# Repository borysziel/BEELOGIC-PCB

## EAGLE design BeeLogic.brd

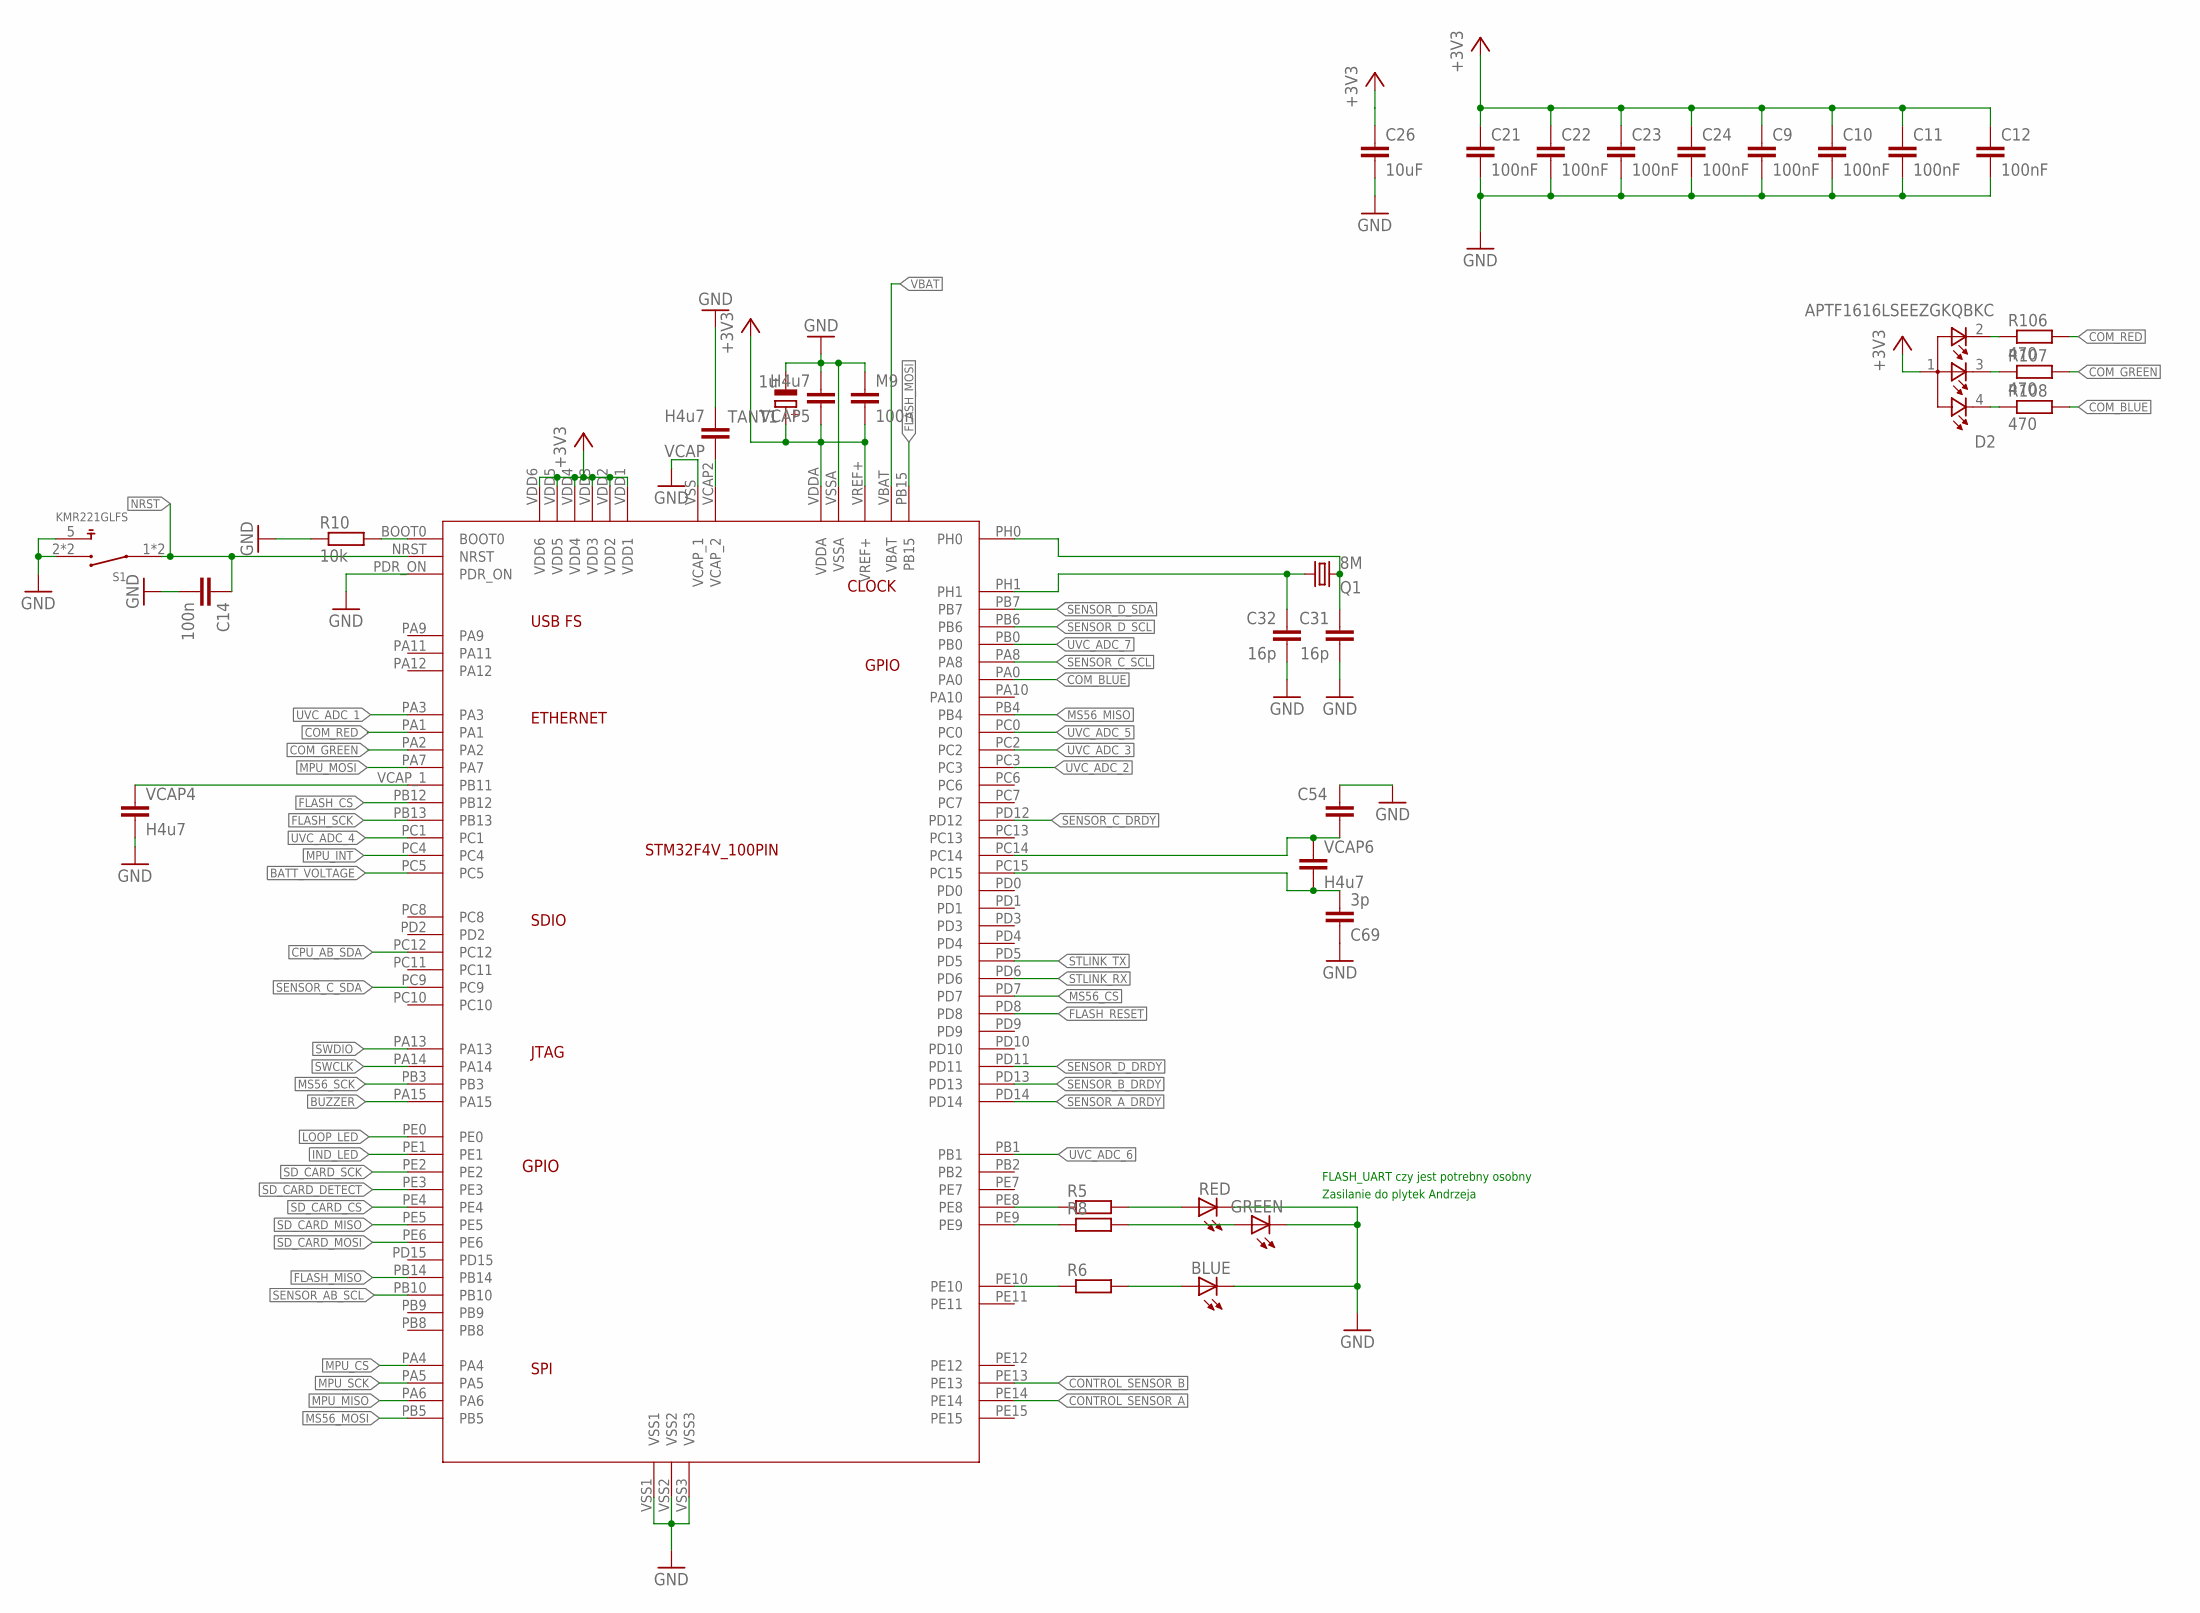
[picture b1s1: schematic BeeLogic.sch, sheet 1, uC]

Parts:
BLUE: LEDCHIPLED_0603; CHIPLED_0603
C9, C10, C11, C12, C21, C22, C23, C24: 100nF; C0603K
C14: 100n; C0603K
C26: 10uF; C0805K
C31, C32: 16p; C0603K
C54, C69: 3p; C0603K
D2: APTF1616LSEEZGKQBKC; LEDSC160X160X070-4N
GREEN: LEDCHIPLED_0603; CHIPLED_0603
M9: 100n; C0603K
Q1: 8M; CTS406
R5, R6, R8: R-EU_R0603; R0603
R10: 10k; R0603
R106, R107, R108: 470; R0603
RED: LEDCHIPLED_0603; CHIPLED_0603
S1: KMR221GLFS; SW_KMR221GLFS
STM32F446VET1: STM32F4V_100PIN_GPSBOARD; LQFP100
TANT1: 1u; SMC_A
VCAP, VCAP4, VCAP5, VCAP6: H4u7; C0805K

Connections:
+3V3: C9.1, C10.1, C11.1, C12.1, C21.1, C22.1, C23.1, C24.1, C26.1, D2.1, M9.2, STM32F446VET1.VDD1, STM32F446VET1.VDD2, STM32F446VET1.VDD3, STM32F446VET1.VDD4, STM32F446VET1.VDD5, STM32F446VET1.VDD6, STM32F446VET1.VDDA, STM32F446VET1.VREF+, TANT1.+, VCAP5.1; also elsewhere on the board
BATT_VOLTAGE: STM32F446VET1.PC5; also elsewhere on the board
BUZZER: STM32F446VET1.PA15; also elsewhere on the board
COM_BLUE: R108.2, STM32F446VET1.PA0
COM_GREEN: R107.2, STM32F446VET1.PA2
COM_RED: R106.2, STM32F446VET1.PA1
CONTROL_SENSOR_A: STM32F446VET1.PE14; also elsewhere on the board
CONTROL_SENSOR_B: STM32F446VET1.PE13; also elsewhere on the board
CPU_AB_SDA: STM32F446VET1.PC12; also elsewhere on the board
FLASH_CS: STM32F446VET1.PB12; also elsewhere on the board
FLASH_MISO: STM32F446VET1.PB14; also elsewhere on the board
FLASH_MOSI: STM32F446VET1.PB15; also elsewhere on the board
FLASH_RESET: STM32F446VET1.PD8; also elsewhere on the board
FLASH_SCK: STM32F446VET1.PB13; also elsewhere on the board
GND: BLUE.C, C9.2, C10.2, C11.2, C12.2, C14.2, C21.2, C22.2, C23.2, C24.2, C26.2, C31.2, C32.2, C54.2, C69.1, GREEN.C, M9.1, R10.1, RED.C, S1.2 (3), S1.3, S1.5, STM32F446VET1.PDR_ON, STM32F446VET1.VSS (VCAP_1), STM32F446VET1.VSS1, STM32F446VET1.VSS2, STM32F446VET1.VSS3, STM32F446VET1.VSSA, TANT1.-, VCAP.2, VCAP4.2, VCAP5.2; also elsewhere on the board
IND_LED: STM32F446VET1.PE1; also elsewhere on the board
LOOP_LED: STM32F446VET1.PE0; also elsewhere on the board
MPU_CS: STM32F446VET1.PA4; also elsewhere on the board
MPU_INT: STM32F446VET1.PC4; also elsewhere on the board
MPU_MISO: STM32F446VET1.PA6; also elsewhere on the board
MPU_MOSI: STM32F446VET1.PA7; also elsewhere on the board
MPU_SCK: STM32F446VET1.PA5; also elsewhere on the board
MS56_CS: STM32F446VET1.PD7; also elsewhere on the board
MS56_MISO: STM32F446VET1.PB4; also elsewhere on the board
MS56_MOSI: STM32F446VET1.PB5; also elsewhere on the board
MS56_SCK: STM32F446VET1.PB3; also elsewhere on the board
unnamed: R5.1, STM32F446VET1.PE8
unnamed: R8.1, STM32F446VET1.PE9
unnamed: R6.1, STM32F446VET1.PE10
unnamed: R10.2, STM32F446VET1.BOOT0
unnamed: C31.1, Q1.3 (2), STM32F446VET1.PH0
unnamed: C32.1, Q1.1, STM32F446VET1.PH1
unnamed: R5.2, RED.A
unnamed: GREEN.A, R8.2
unnamed: BLUE.A, R6.2
unnamed: STM32F446VET1.VCAP2 (VCAP_2), VCAP.1
unnamed: STM32F446VET1.VCAP_1 (PB11), VCAP4.1
unnamed: D2.2, R106.1
unnamed: D2.3, R107.1
unnamed: D2.4, R108.1
unnamed: C54.1, STM32F446VET1.PC14, VCAP6.1
unnamed: C69.2, STM32F446VET1.PC15, VCAP6.2
NRST: C14.1, S1.1, S1.4 (1), STM32F446VET1.NRST; also elsewhere on the board
SD_CARD_CS: STM32F446VET1.PE4; also elsewhere on the board
SD_CARD_DETECT: STM32F446VET1.PE3; also elsewhere on the board
SD_CARD_MISO: STM32F446VET1.PE5; also elsewhere on the board
SD_CARD_MOSI: STM32F446VET1.PE6; also elsewhere on the board
SD_CARD_SCK: STM32F446VET1.PE2; also elsewhere on the board
SENSOR_AB_SCL: STM32F446VET1.PB10; also elsewhere on the board
SENSOR_A_DRDY: STM32F446VET1.PD14; also elsewhere on the board
SENSOR_B_DRDY: STM32F446VET1.PD13; also elsewhere on the board
SENSOR_C_DRDY: STM32F446VET1.PD12; also elsewhere on the board
SENSOR_C_SCL: STM32F446VET1.PA8; also elsewhere on the board
SENSOR_C_SDA: STM32F446VET1.PC9; also elsewhere on the board
SENSOR_D_DRDY: STM32F446VET1.PD11; also elsewhere on the board
SENSOR_D_SCL: STM32F446VET1.PB6; also elsewhere on the board
SENSOR_D_SDA: STM32F446VET1.PB7; also elsewhere on the board
STLINK_RX: STM32F446VET1.PD6; also elsewhere on the board
STLINK_TX: STM32F446VET1.PD5; also elsewhere on the board
SWCLK: STM32F446VET1.PA14; also elsewhere on the board
SWDIO: STM32F446VET1.PA13; also elsewhere on the board
UVC_ADC_1: STM32F446VET1.PA3; also elsewhere on the board
UVC_ADC_2: STM32F446VET1.PC3; also elsewhere on the board
UVC_ADC_3: STM32F446VET1.PC2; also elsewhere on the board
UVC_ADC_4: STM32F446VET1.PC1; also elsewhere on the board
UVC_ADC_5: STM32F446VET1.PC0; also elsewhere on the board
UVC_ADC_6: STM32F446VET1.PB1; also elsewhere on the board
UVC_ADC_7: STM32F446VET1.PB0; also elsewhere on the board
VBAT: STM32F446VET1.VBAT; also elsewhere on the board

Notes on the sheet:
FLASH_UART czy jest potrebny osobny
Zasilanie do plytek Andrzeja

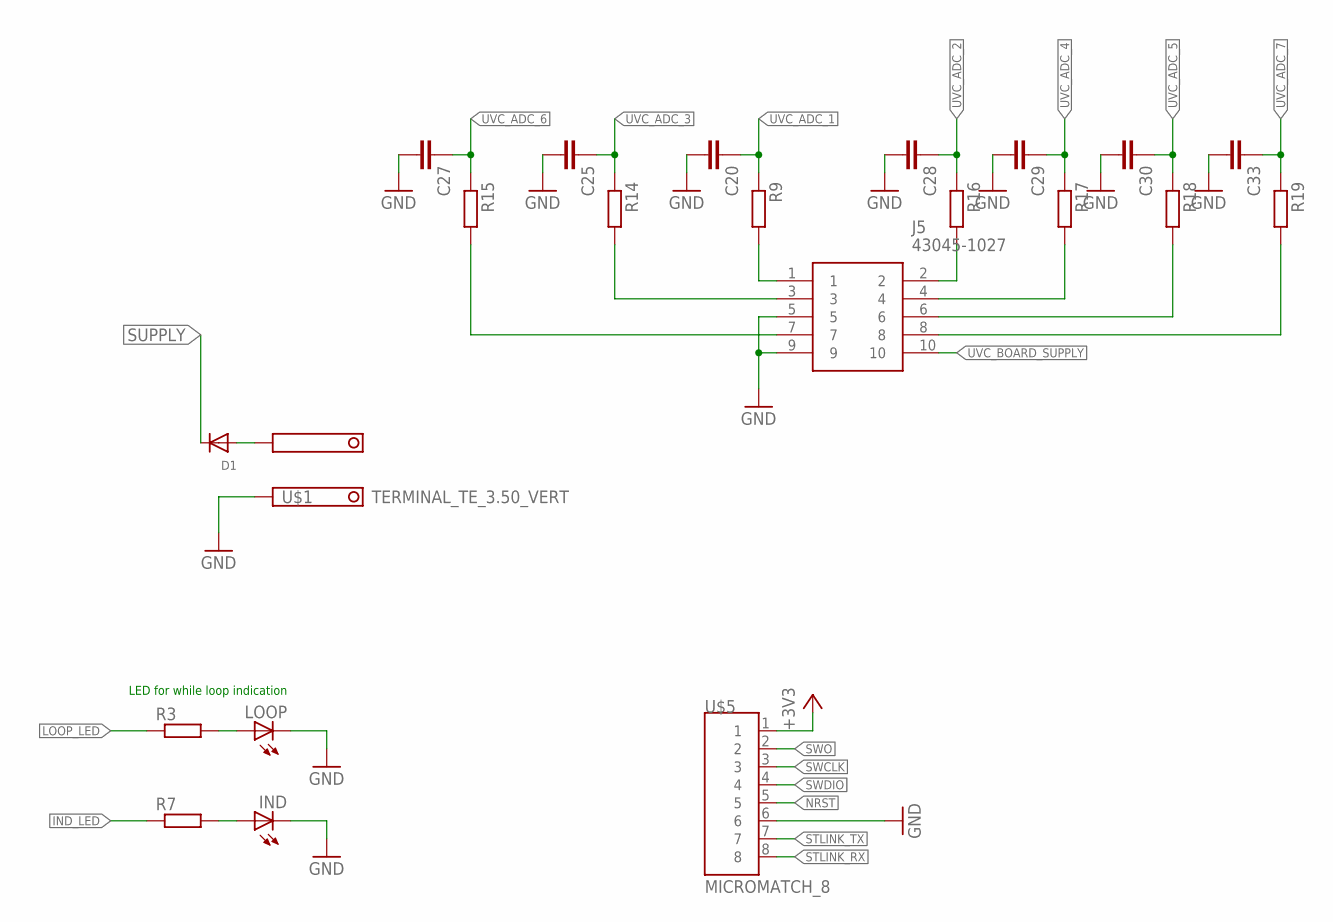
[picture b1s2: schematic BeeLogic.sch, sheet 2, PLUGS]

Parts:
C20, C25, C27, C28, C29, C30, C33: C-EUC0603; C0603
D1: DIODE_SOD-123FL; SOD-123FL
IND: LEDCHIPLED_0603; CHIPLED_0603
J5: 43045-1027; 43045-1028_1
LOOP: LEDCHIPLED_0603; CHIPLED_0603
R3, R7, R9, R14, R15, R16, R17, R18, R19: R-EU_R0603; R0603
U$1: TERMINAL_TE_3.50_VERT; TE_3.5_TERMINAL_VERT
U$5: MICROMATCH_8

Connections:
+3V3: U$5.1; also elsewhere on the board
GND: C20.2, C25.2, C27.2, C28.2, C29.2, C30.2, C33.2, IND.C, J5.5, J5.9, LOOP.C, U$1.P$2 (K1), U$5.6; also elsewhere on the board
IND_LED: R7.1; also elsewhere on the board
LOOP_LED: R3.1; also elsewhere on the board
unnamed: LOOP.A, R3.2
unnamed: D1.A, U$1.P$1 (K)
unnamed: IND.A, R7.2
unnamed: J5.1, R9.2
unnamed: J5.7, R15.2
unnamed: J5.3, R14.2
unnamed: J5.2, R16.2
unnamed: J5.4, R17.2
unnamed: J5.6, R18.2
unnamed: J5.8, R19.2
NRST: U$5.5; also elsewhere on the board
STLINK_RX: U$5.8; also elsewhere on the board
STLINK_TX: U$5.7; also elsewhere on the board
SUPPLY: D1.C; also elsewhere on the board
SWCLK: U$5.3; also elsewhere on the board
SWDIO: U$5.4; also elsewhere on the board
SWO: U$5.2
UVC_ADC_1: C20.1, R9.1; also elsewhere on the board
UVC_ADC_2: C28.1, R16.1; also elsewhere on the board
UVC_ADC_3: C25.1, R14.1; also elsewhere on the board
UVC_ADC_4: C29.1, R17.1; also elsewhere on the board
UVC_ADC_5: C30.1, R18.1; also elsewhere on the board
UVC_ADC_6: C27.1, R15.1; also elsewhere on the board
UVC_ADC_7: C33.1, R19.1; also elsewhere on the board
UVC_BOARD_SUPPLY: J5.10; also elsewhere on the board

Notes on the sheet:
LED for while loop indication

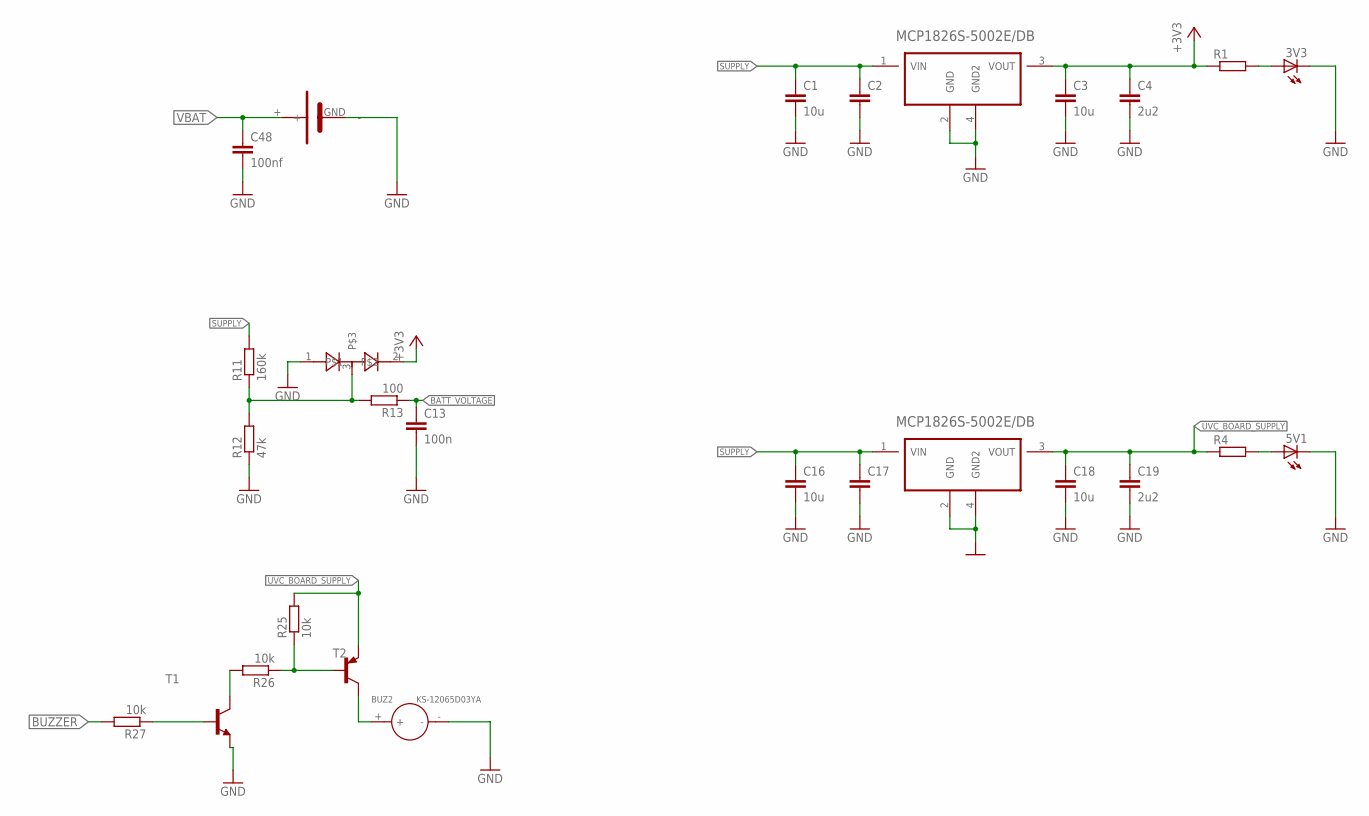
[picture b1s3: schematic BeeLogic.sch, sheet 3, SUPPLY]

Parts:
3V3, 5V1: LEDCHIPLED_0603; CHIPLED_0603
BUZ2: KS-12065D03YA; BZ2-7.6-D12.0XH6.5MM
C1, C3, C16, C18: 10u; C0805K
C2, C17: C-EUC0805K; C0805K
C4, C19: 2u2; C0805K
C13: 100n; C0603
C48: 100nf; C0805K
R1, R4: R-EU_R0603; R0603
R11: 160k; R0603
R12: 47k; R0603
R13: 100; R0603
R25, R26, R27: 10k; R0603
T1: BCW81-NPN-SOT23-BEC; SOT23-BEC
T2: BC807-16-PNP-SOT23-BEC; SOT23-BEC
U1, U3: MCP1826S-5002E/DB; SOT230P700X180-4N
U$16: BAS40W-04; SOT65P210X110-3N
U$32: CR1220_POZ

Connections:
+3V3: C3.1, C4.1, R1.1, U1.3 (VOUT), U$16.2; also elsewhere on the board
BATT_VOLTAGE: C13.1, R13.1; also elsewhere on the board
BUZZER: R27.2; also elsewhere on the board
GND: 3V3.C, 5V1.C, BUZ2.-, C1.2, C2.2, C3.2, C4.2, C13.2, C16.2, C17.2, C18.2, C19.2, C48.2, R12.1, T1.E, U1.2 (GND), U1.4 (GND2), U3.2 (GND), U3.4 (GND2), U$16.1, U$32.GND (-); also elsewhere on the board
unnamed: 3V3.A, R1.2
unnamed: 5V1.A, R4.2
unnamed: R11.1, R12.2, R13.2, U$16.3
unnamed: R25.1, R26.1, T2.B
unnamed: BUZ2.+, T2.C
unnamed: R26.2, T1.C
unnamed: R27.1, T1.B
SUPPLY: C1.1, C2.1, C16.1, C17.1, R11.2, U1.1 (VIN), U3.1 (VIN); also elsewhere on the board
UVC_BOARD_SUPPLY: C18.1, C19.1, R4.1, R25.2, T2.E, U3.3 (VOUT); also elsewhere on the board
VBAT: C48.1, U$32.+; also elsewhere on the board

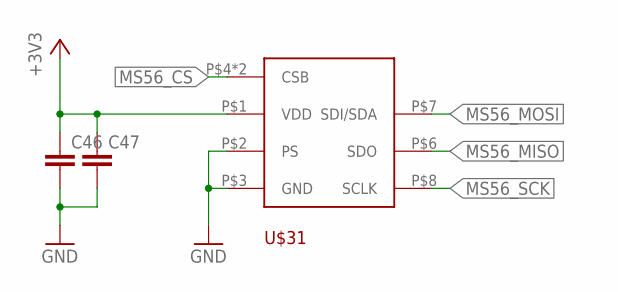
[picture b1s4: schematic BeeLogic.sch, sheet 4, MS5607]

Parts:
C46, C47: C-EUC0603; C0603
U$31: MS56XX

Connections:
+3V3: C46.1, C47.1, U$31.P$1 (VDD); also elsewhere on the board
GND: C46.2, C47.2, U$31.P$2 (PS), U$31.P$3 (GND); also elsewhere on the board
MS56_CS: U$31.P$4 (CSB), U$31.P$5 (CSB); also elsewhere on the board
MS56_MISO: U$31.P$6 (SDO); also elsewhere on the board
MS56_MOSI: U$31.P$7 (SDI/SDA); also elsewhere on the board
MS56_SCK: U$31.P$8 (SCLK); also elsewhere on the board

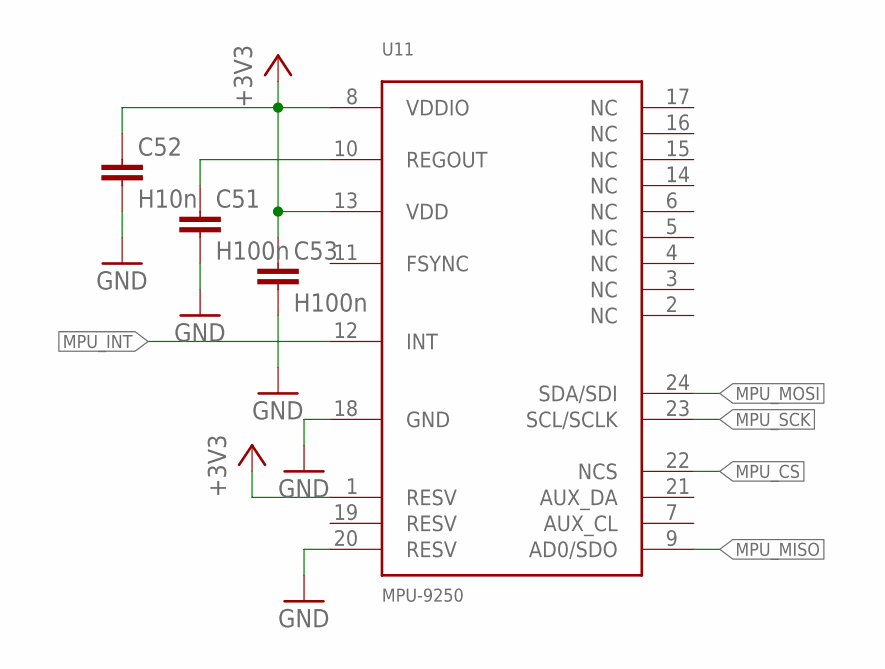
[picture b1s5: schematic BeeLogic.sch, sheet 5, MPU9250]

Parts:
C51, C53: H100n; C0603K
C52: H10n; C0603K
U11: MPU-9250

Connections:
+3V3: C52.1, C53.1, U11.1 (RESV), U11.8 (VDDIO), U11.13 (VDD); also elsewhere on the board
GND: C51.2, C52.2, C53.2, U11.18 (GND), U11.20 (RESV); also elsewhere on the board
MPU_CS: U11.22 (NCS); also elsewhere on the board
MPU_INT: U11.12 (INT); also elsewhere on the board
MPU_MISO: U11.9 (AD0/SDO); also elsewhere on the board
MPU_MOSI: U11.24 (SDA/SDI); also elsewhere on the board
MPU_SCK: U11.23 (SCL/SCLK); also elsewhere on the board
unnamed: C51.1, U11.10 (REGOUT)

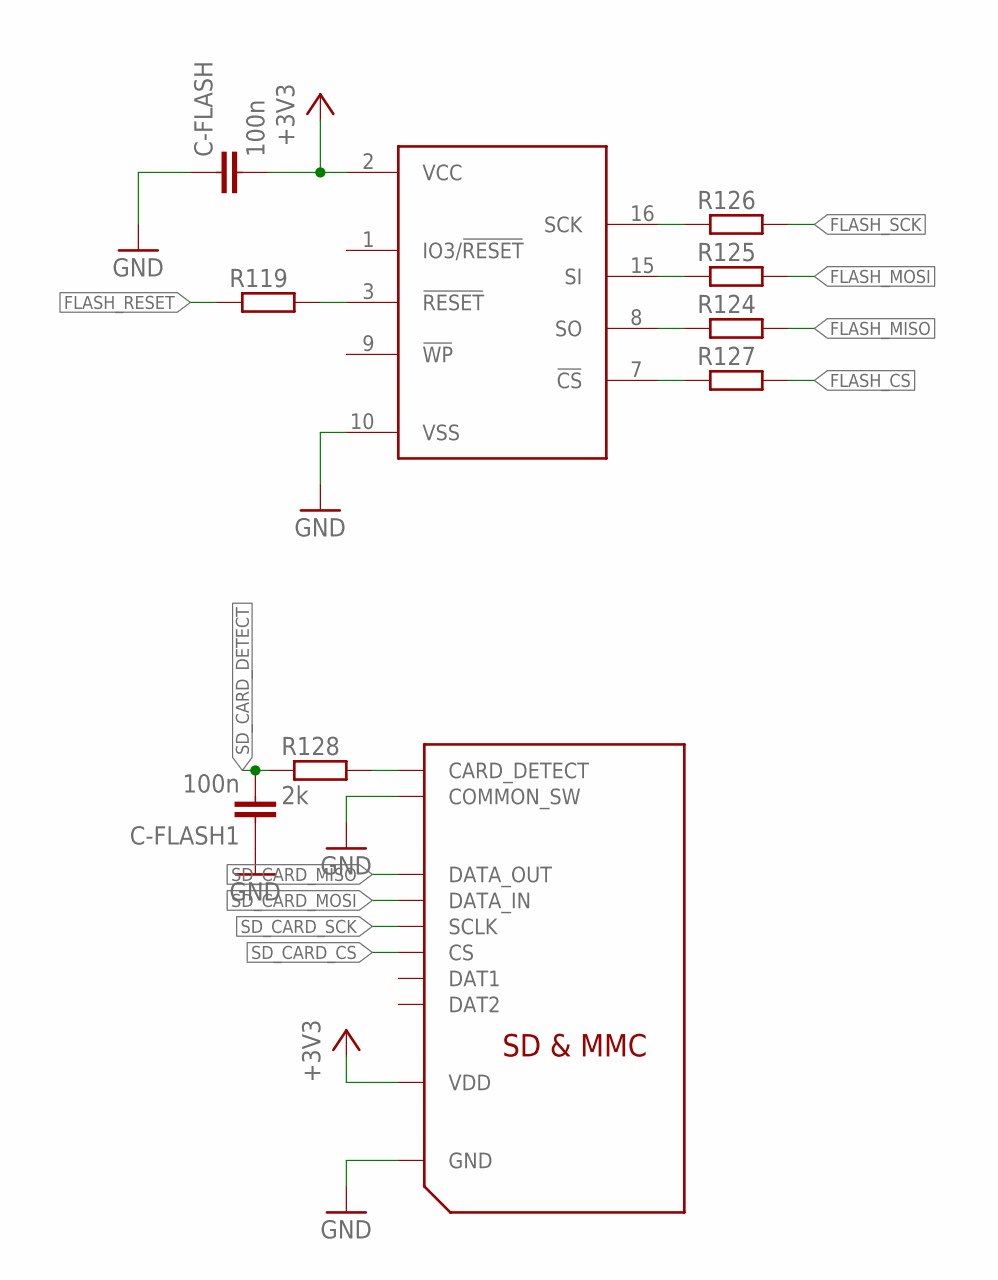
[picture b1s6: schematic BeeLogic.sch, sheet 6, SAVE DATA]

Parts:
C-FLASH, C-FLASH1: 100n; C0603K
R119, R124, R125, R126, R127: R-EU_R0603; R0603
R128: 2k; R0603
U$2: S25FLX; SOIC16
U$4: MOLEX_MICRO_SD_503182-1853

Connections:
+3V3: C-FLASH.2, U$2.2 (VCC), U$4.PIN4 (VDD); also elsewhere on the board
FLASH_CS: R127.2; also elsewhere on the board
FLASH_MISO: R124.2; also elsewhere on the board
FLASH_MOSI: R125.2; also elsewhere on the board
FLASH_RESET: R119.1; also elsewhere on the board
FLASH_SCK: R126.2; also elsewhere on the board
GND: C-FLASH.1, C-FLASH1.1, U$2.10 (VSS), U$4.DETECT_GND (COMMON_SW), U$4.PIN6 (GND); also elsewhere on the board
unnamed: R126.1, U$2.16 (SCK)
unnamed: R125.1, U$2.15 (SI)
unnamed: R124.1, U$2.8 (SO)
unnamed: R127.1, U$2.7 (!CS)
unnamed: R119.2, U$2.3 (!RESET)
unnamed: R128.2, U$4.DETECT (CARD_DETECT)
SD_CARD_CS: U$4.PIN2 (CS); also elsewhere on the board
SD_CARD_DETECT: C-FLASH1.2, R128.1; also elsewhere on the board
SD_CARD_MISO: U$4.PIN7 (DATA_OUT); also elsewhere on the board
SD_CARD_MOSI: U$4.PIN3 (DATA_IN); also elsewhere on the board
SD_CARD_SCK: U$4.PIN5 (SCLK); also elsewhere on the board

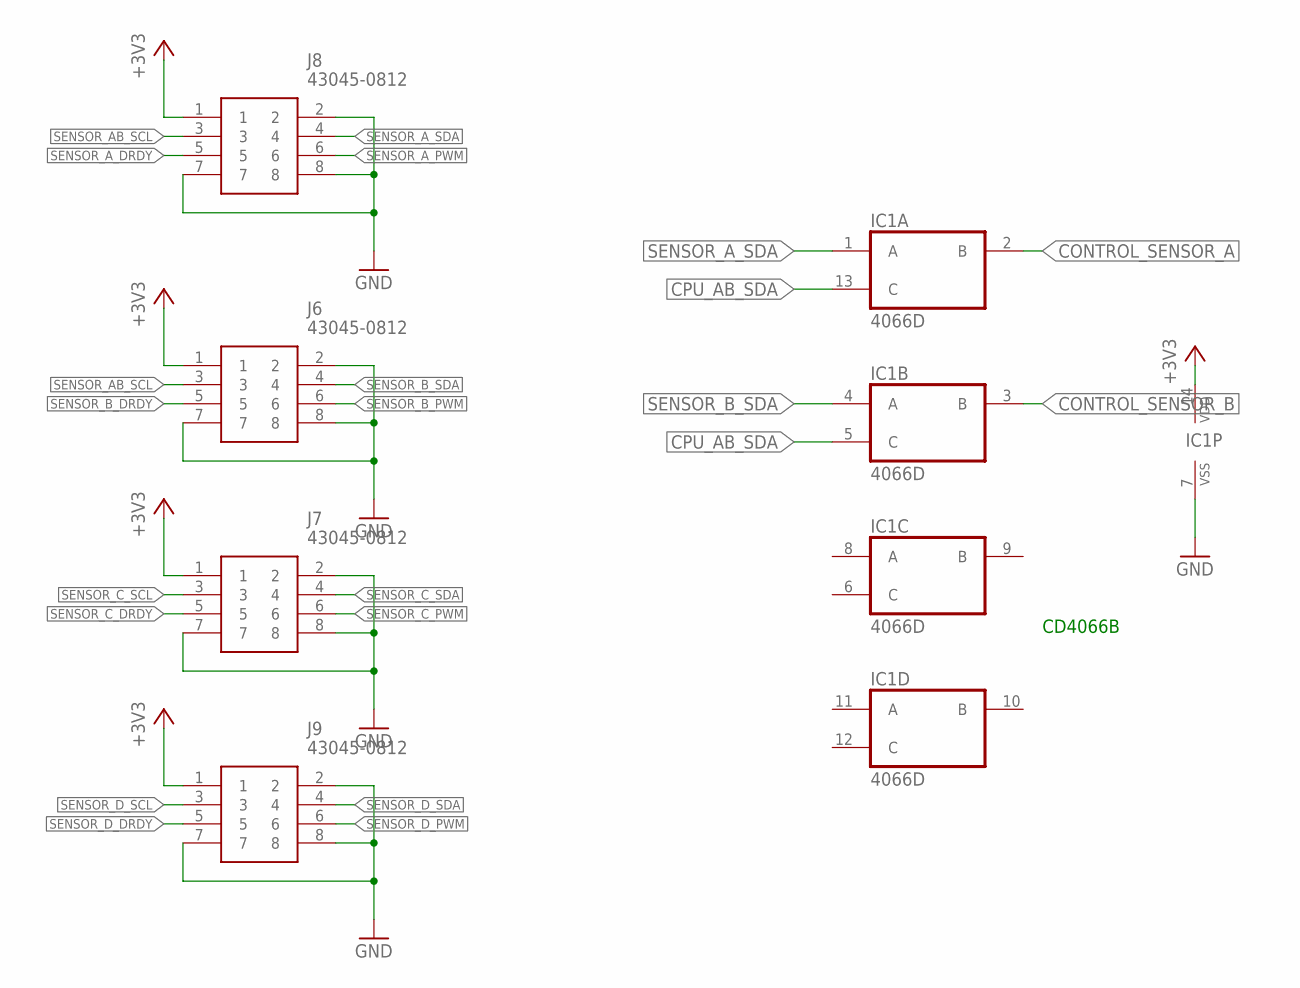
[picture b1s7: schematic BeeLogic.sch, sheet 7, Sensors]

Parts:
IC1: 4066D; SO14
J6, J7, J8, J9: 43045-0812; 430450812

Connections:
+3V3: IC1.14 (VDD), J6.1, J7.1, J8.1, J9.1; also elsewhere on the board
CONTROL_SENSOR_A: IC1.2 (B); also elsewhere on the board
CONTROL_SENSOR_B: IC1.3 (B); also elsewhere on the board
CPU_AB_SDA: IC1.5 (C), IC1.13 (C); also elsewhere on the board
GND: IC1.7 (VSS), J6.2, J6.7, J6.8, J7.2, J7.7, J7.8, J8.2, J8.7, J8.8, J9.2, J9.7, J9.8; also elsewhere on the board
SENSOR_AB_SCL: J6.3, J8.3; also elsewhere on the board
SENSOR_A_DRDY: J8.5; also elsewhere on the board
SENSOR_A_PWM: J8.6
SENSOR_A_SDA: IC1.1 (A), J8.4
SENSOR_B_DRDY: J6.5; also elsewhere on the board
SENSOR_B_PWM: J6.6
SENSOR_B_SDA: IC1.4 (A), J6.4
SENSOR_C_DRDY: J7.5; also elsewhere on the board
SENSOR_C_PWM: J7.6
SENSOR_C_SCL: J7.3; also elsewhere on the board
SENSOR_C_SDA: J7.4; also elsewhere on the board
SENSOR_D_DRDY: J9.5; also elsewhere on the board
SENSOR_D_PWM: J9.6
SENSOR_D_SCL: J9.3; also elsewhere on the board
SENSOR_D_SDA: J9.4; also elsewhere on the board

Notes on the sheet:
CD4066B

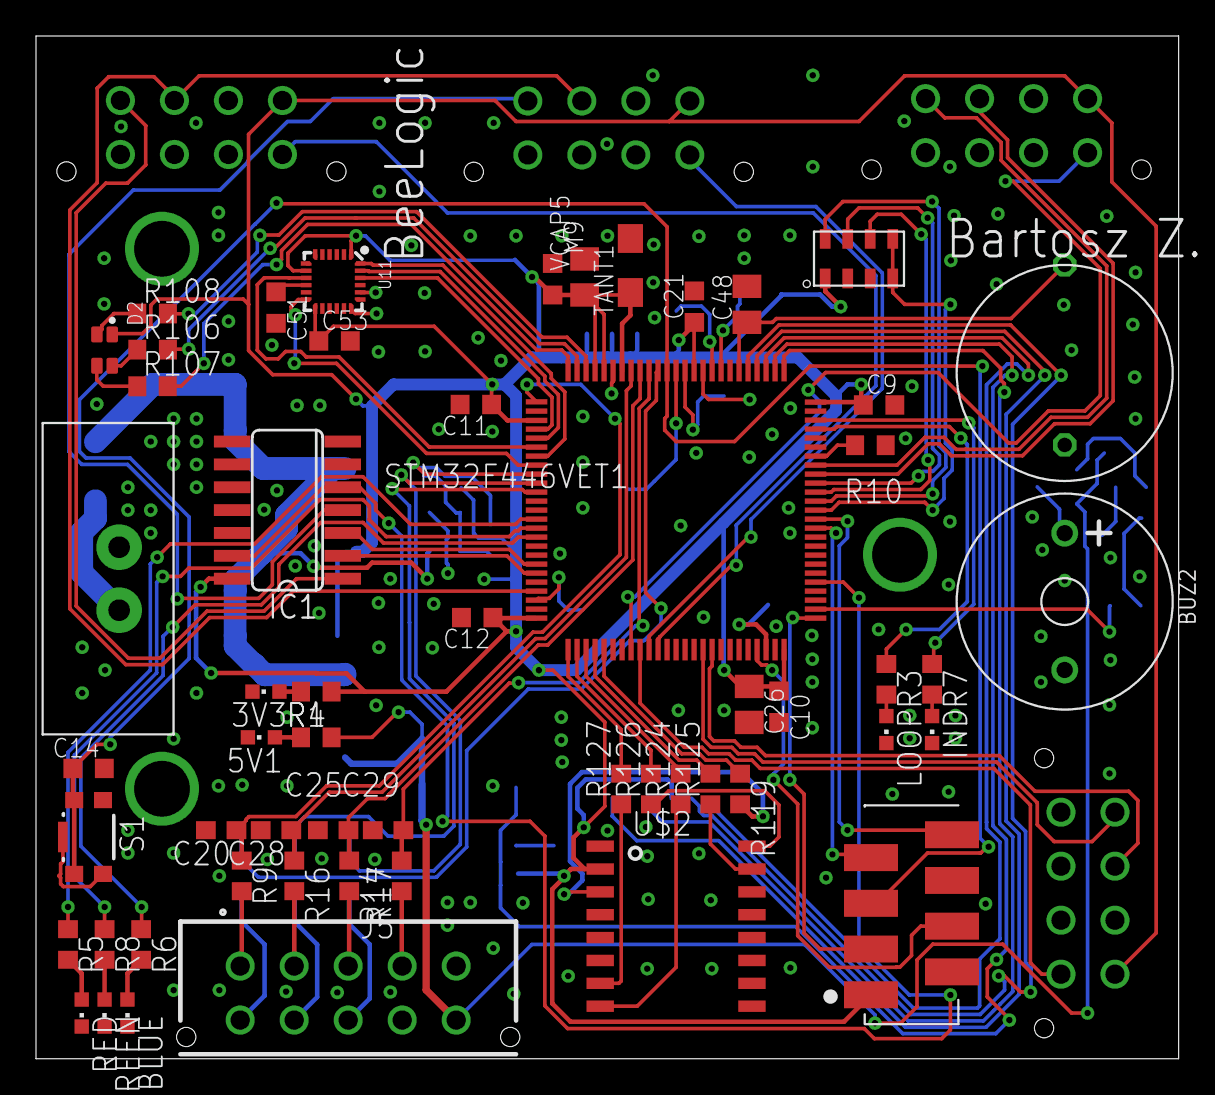
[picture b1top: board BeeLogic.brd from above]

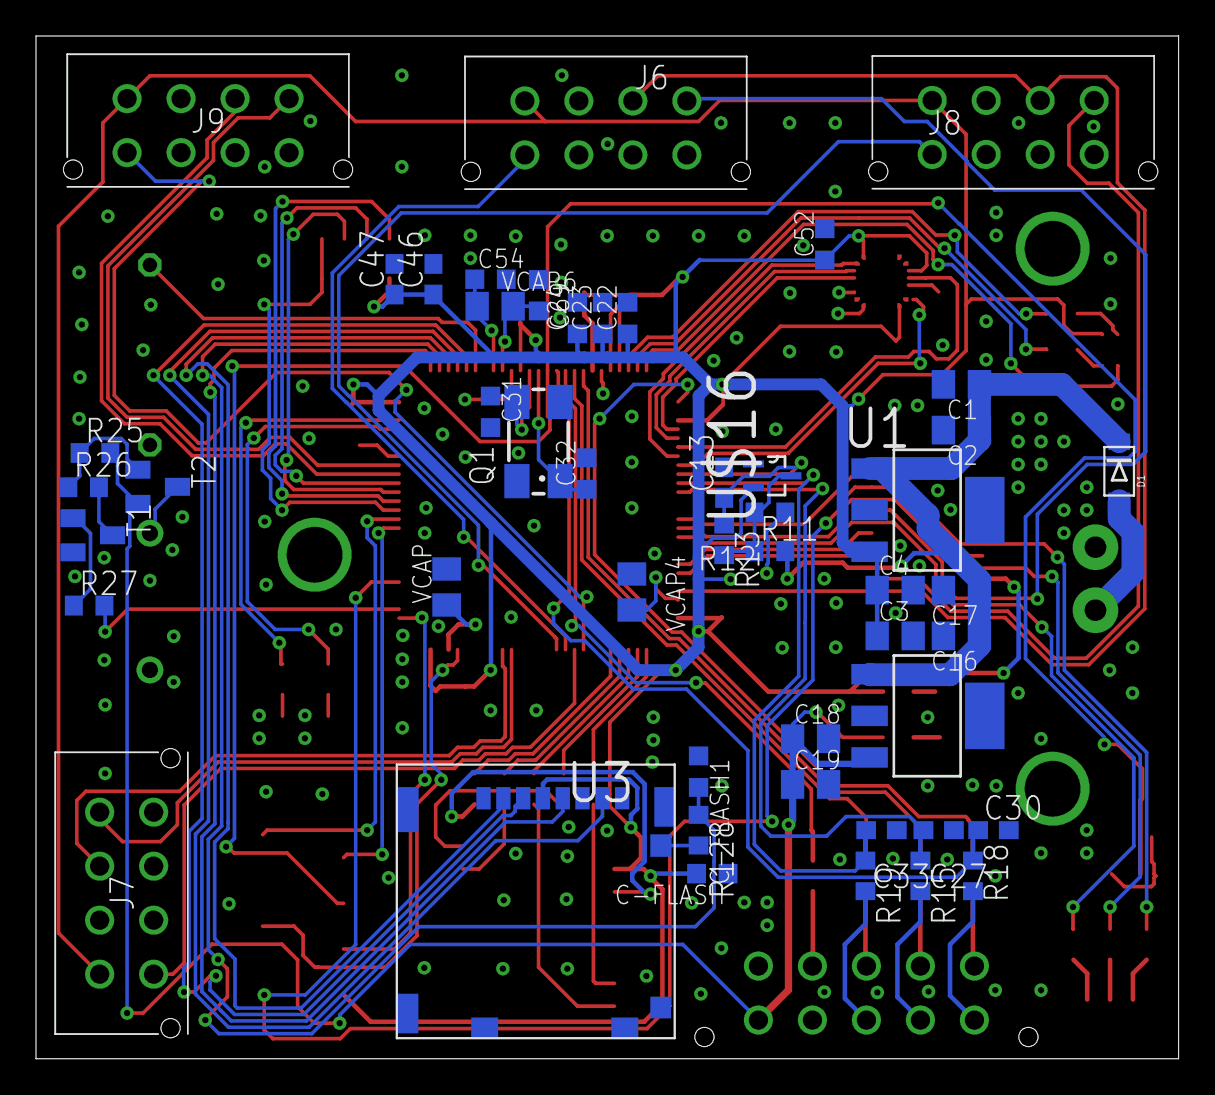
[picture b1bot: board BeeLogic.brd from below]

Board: 2 copper layers, 63.5 x 56.8 mm, 105 parts (49 on the bottom side), 97 nets.

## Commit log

2019-08-27 last version

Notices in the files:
parts and their libraries:
SparkFun-Aesthetics: Licensing: CC v3.0 Share-Alike You are welcome to use this library for commercial purposes.
